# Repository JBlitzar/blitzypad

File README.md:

# blitzypad

My starter hackpad project for Blueprint! Has four keys in a grid, an extra key, a rotary encoder, and a 128x32 OLED screen.

I don't have a screenshot of my overall project because it doesn't exist physically yet.

I plan to use this for all sorts of things! General use, sure. Probably also music production with that cool rotary encoder (time scrub / volume control). Or maybe even something like gaming or video editing! That's the beauty of circuitpython. It's really easy and you don't have to reflash every time. I may even try to have some dynamic things on the OLED screen down the line... After all, rp2040 can act as an arbitrary usb device! I've [done](https://github.com/JBlitzar/pd-usb-uvc) [some](https://github.com/JBlitzar/picoducky) [projects](https://github.com/JBlitzar/pd-quad-draw) with those as a part of picoducky ysws. This is really cool because we've got some additional hardware IO (namely the keys, rotary encoder, leds, and screen.)

<table width="100%">
    <tr>
    <td></td>
        <td>
            
        </td>
        <td>
            
        </td>
    </tr>
</table>

## Case

_made in Fusion 360_

I have access to a laser cutter + 3d printer, so I won't need these to be shipped.

## Schematic

_made in Kicad_

### PCB:

> I had some fun with the graphics, haha

_clean PCB without silkscreen:_

### Schematic:

> (sorry it's a bit messy)

### Footprints:

## BOM:

- 5 Cherry MX Switches
- 5 Keycaps
- 2 SK6812MINI-E LEDs
- 1 0.91" SSD1306 128x32 I2C OLED Display
- 1 Alps rotary encoder, EC12E with switch, vertical shaft.
- 1 XIAO RP2040
- 1 Case
- 4 bolts to hold the case together, I guess?
- 1 male-male USB-C data cable (to plug the xiao in)

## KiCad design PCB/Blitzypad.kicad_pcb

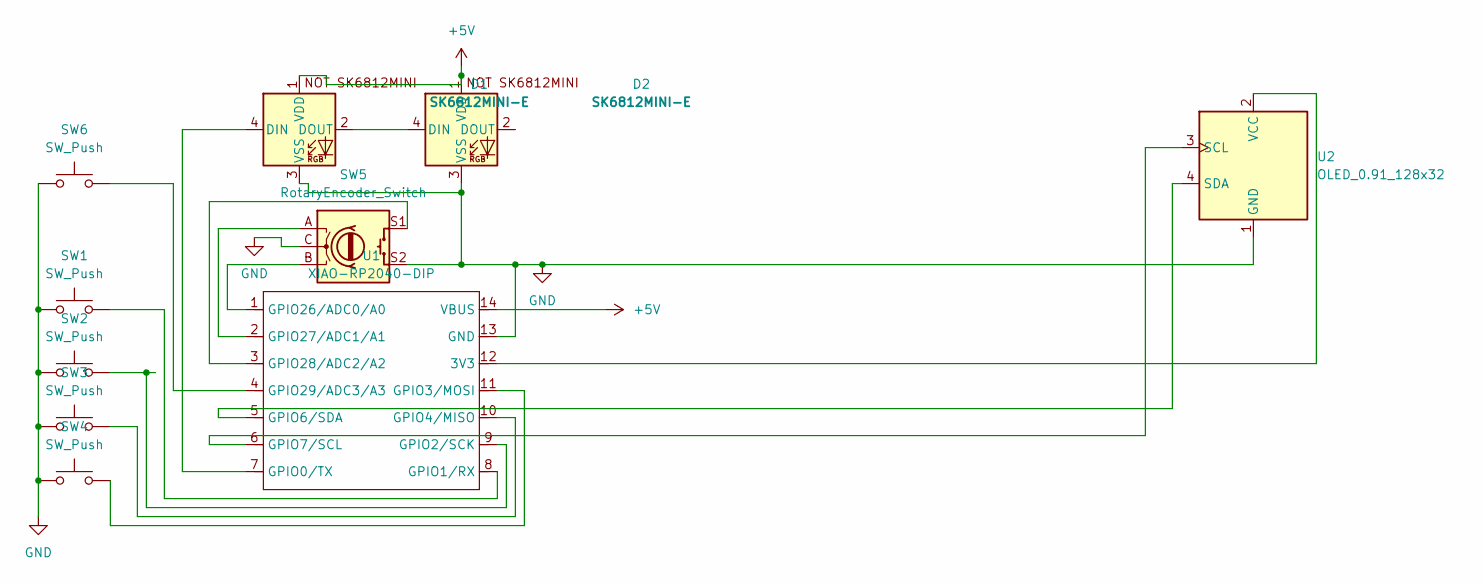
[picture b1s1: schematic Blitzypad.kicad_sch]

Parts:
D1, D2: SK6812MINI-E; SK6812MINI-E_fixed
SW1, SW2, SW3, SW4, SW6: SW_Push; SW_Cherry_MX_1.00u_PCB
SW5: RotaryEncoder_Switch; RotaryEncoder_Alps_EC11E-Switch_Vertical_H20mm_CircularMoun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
U1: XIAO-RP2040-DIP
U2: OLED_0.91_128x32

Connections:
+5V: D1.1 (VDD), D2.1 (VDD), U1.14 (VBUS)
GND: D1.3 (VSS), D2.3 (VSS), SW1.1, SW2.1, SW3.1, SW4.1, SW5.C, SW5.S2, SW6.1, U1.13 (GND), U2.1 (GND)
unnamed: D1.4 (DIN), U1.7 (GPIO0/TX)
unnamed: D1.2 (DOUT), D2.4 (DIN)
unnamed: U1.12 (3V3), U2.2 (VCC)
unnamed: SW1.2, U1.8 (GPIO1/RX)
unnamed: SW2.2, U1.9 (GPIO2/SCK)
unnamed: SW4.2, U1.11 (GPIO3/MOSI)
unnamed: SW3.2, U1.10 (GPIO4/MISO)
unnamed: U1.5 (GPIO6/SDA), U2.4 (SDA)
unnamed: U1.6 (GPIO7/SCL), U2.3 (SCL)
unnamed: SW5.B, U1.1 (GPIO26/ADC0/A0)
unnamed: SW5.A, U1.2 (GPIO27/ADC1/A1)
unnamed: SW5.S1, U1.3 (GPIO28/ADC2/A2)
unnamed: SW6.2, U1.4 (GPIO29/ADC3/A3)

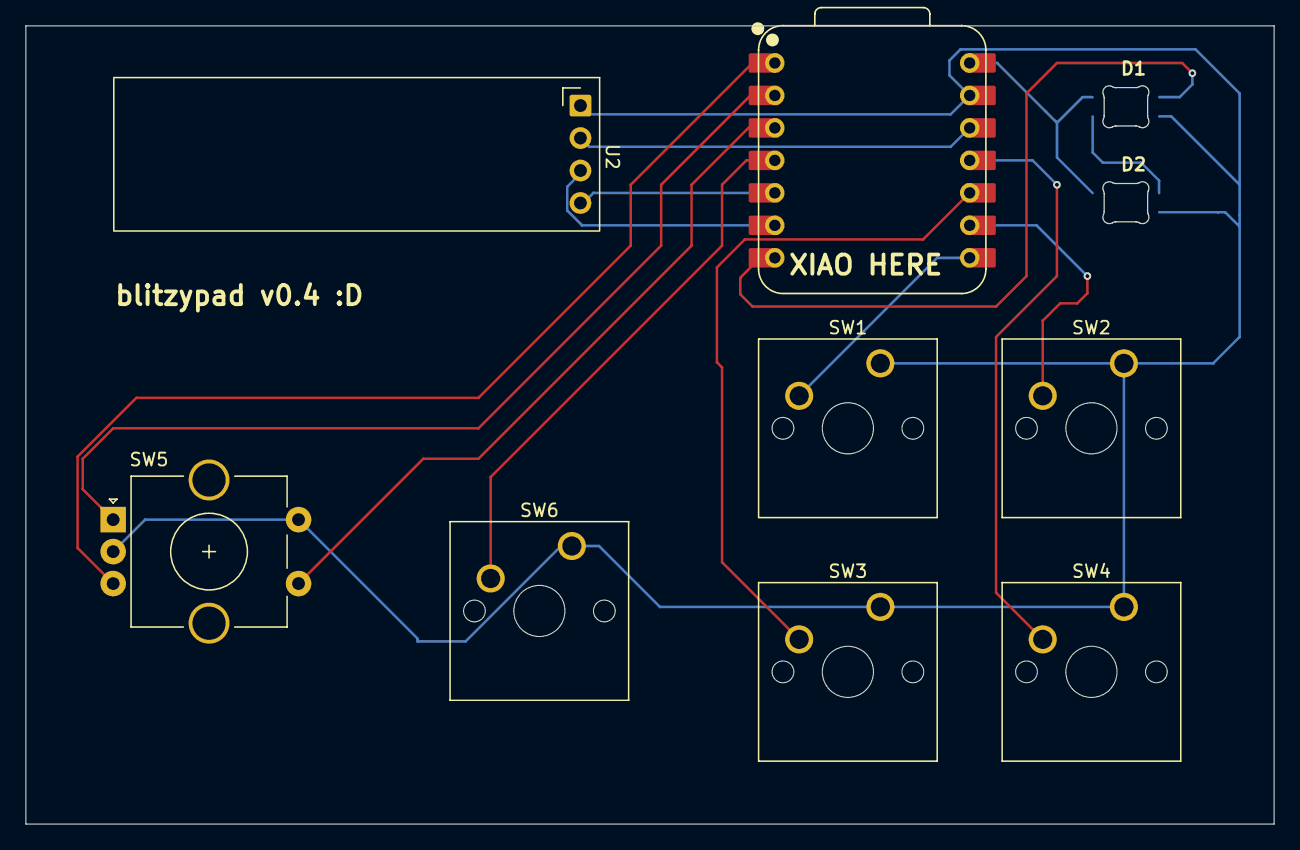
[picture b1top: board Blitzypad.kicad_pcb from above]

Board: 2 copper layers, 97.6 x 62.4 mm, 10 parts (0 on the bottom side), 15 nets.

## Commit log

2026-01-05 upload everything
2026-01-05 make firmware
2026-01-05 readme
2026-01-05 Add top and bottom as separate files
2026-01-06 pictures
2026-01-06 Apply fixes according to feedback
2026-01-06 update picture
2026-01-06 small pcb changes to make it look nicer
2026-01-06 new case
2026-01-06 new renders
2026-01-06 better render
2026-01-06 aaaa
2026-01-06 imagmamgaes
2026-01-22 works
2026-01-25 display works
2026-01-27 refactor, works fr
2026-01-27 shortcut
2026-03-15 Remove screenshot from README
    Comment out screenshot in README
2026-03-15 Update project screenshot in README
2026-05-22 figmoids
